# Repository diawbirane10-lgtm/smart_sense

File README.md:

# SmartSense

**Prototype R&D de capteurs industriels — en cours.**

SmartSense est une plateforme de laboratoire pour l'acquisition et le diagnostic de signaux **infrarouges modulés** et **ultrasonores (40 kHz)**. Elle utilise un **STM32G431**, une chaîne analogique dédiée et un **PCB 4 couches** conçu avec KiCad.

## État du projet

| Réalisé | À faire |
|---|---|
| Schémas et PCB KiCad V1 (ERC/DRC : 0 violation signalée) | Fabrication et assemblage de la carte |
| Noyau C : 22 tests réussis sur PC, compilation ARM vérifiée | Intégration firmware et essais sur STM32 |
| Modèles et simulations MATLAB/Simulink | Mesures et validation sur banc |

**Important :** aucun essai physique n'a encore été réalisé. Le prototype n'est pas qualifié pour une application ferroviaire ou de sécurité.

## Fichiers principaux

- [Conception KiCad V1](hardware/V1/SmartSense_V1.kicad_pro) — ouvrir avec **KiCad 10**.
- [Études MATLAB/Simulink](etudes/README.md)
- [Firmware C](firmware/README.md) et [programmation STM32](PROGRAMMATION.md)
- [Prototype et prochaines étapes](ingenierie/PROTOTYPE.md)
- [Revue R&D et limites](ingenierie/revue_RD_20261106/DECISION_ET_REVUE.md)

[Portfolio](https://b-diaw.com)

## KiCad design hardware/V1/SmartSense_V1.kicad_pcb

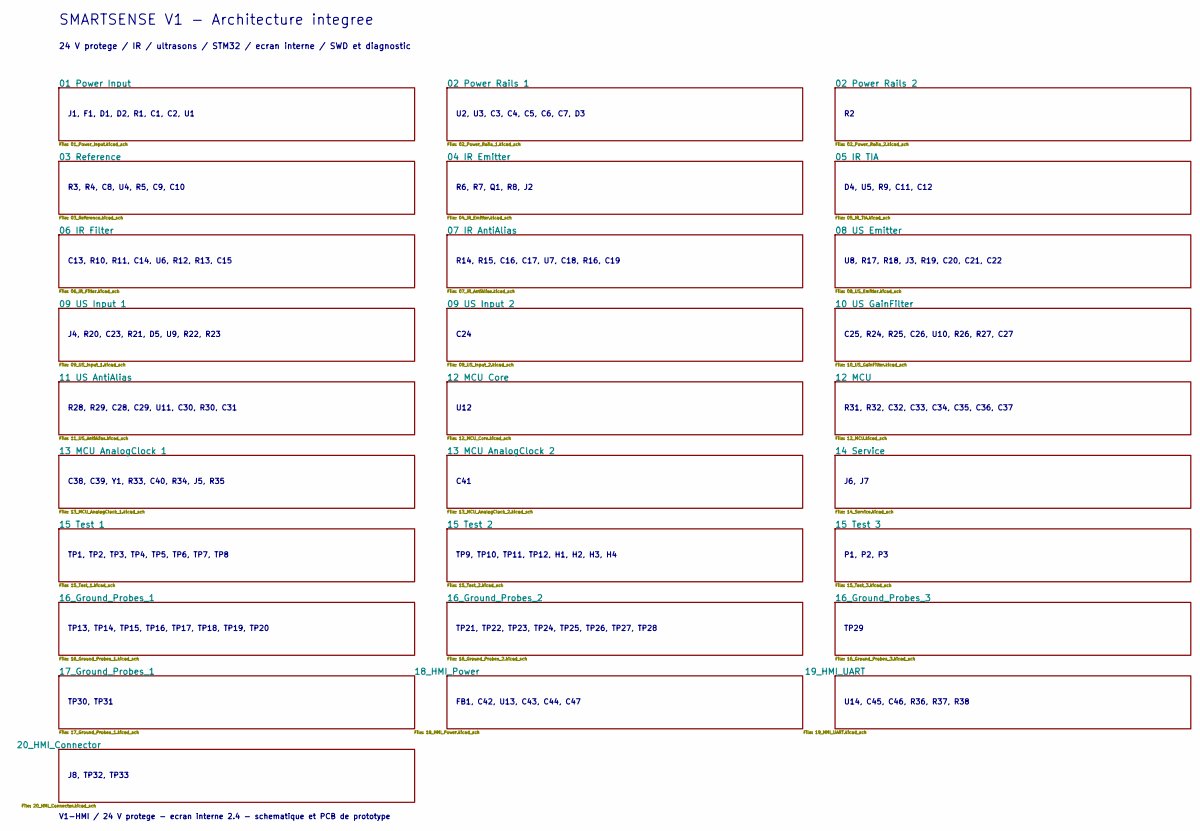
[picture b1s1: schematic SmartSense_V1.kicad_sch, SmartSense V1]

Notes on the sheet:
SMARTSENSE V1 - Architecture integree
24 V protege / IR / ultrasons / STM32 / ecran interne / SWD et diagnostic
V1-HMI / 24 V protege - ecran interne 2.4 - schematique et PCB de prototype
J1, F1, D1, D2, R1, C1, C2, U1
U2, U3, C3, C4, C5, C6, C7, D3
R3, R4, C8, U4, R5, C9, C10
R6, R7, Q1, R8, J2
D4, U5, R9, C11, C12
C13, R10, R11, C14, U6, R12, R13, C15
R14, R15, C16, C17, U7, C18, R16, C19
U8, R17, R18, J3, R19, C20, C21, C22
J4, R20, C23, R21, D5, U9, R22, R23
C24
C25, R24, R25, C26, U10, R26, R27, C27
R28, R29, C28, C29, U11, C30, R30, C31
U12
R31, R32, C32, C33, C34, C35, C36, C37
C38, C39, Y1, R33, C40, R34, J5, R35
C41
J6, J7
TP1, TP2, TP3, TP4, TP5, TP6, TP7, TP8
TP9, TP10, TP11, TP12, H1, H2, H3, H4
P1, P2, P3
TP13, TP14, TP15, TP16, TP17, TP18, TP19, TP20
TP21, TP22, TP23, TP24, TP25, TP26, TP27, TP28
TP29
TP30, TP31
FB1, C42, U13, C43, C44, C47
U14, C45, C46, R36, R37, R38
J8, TP32, TP33

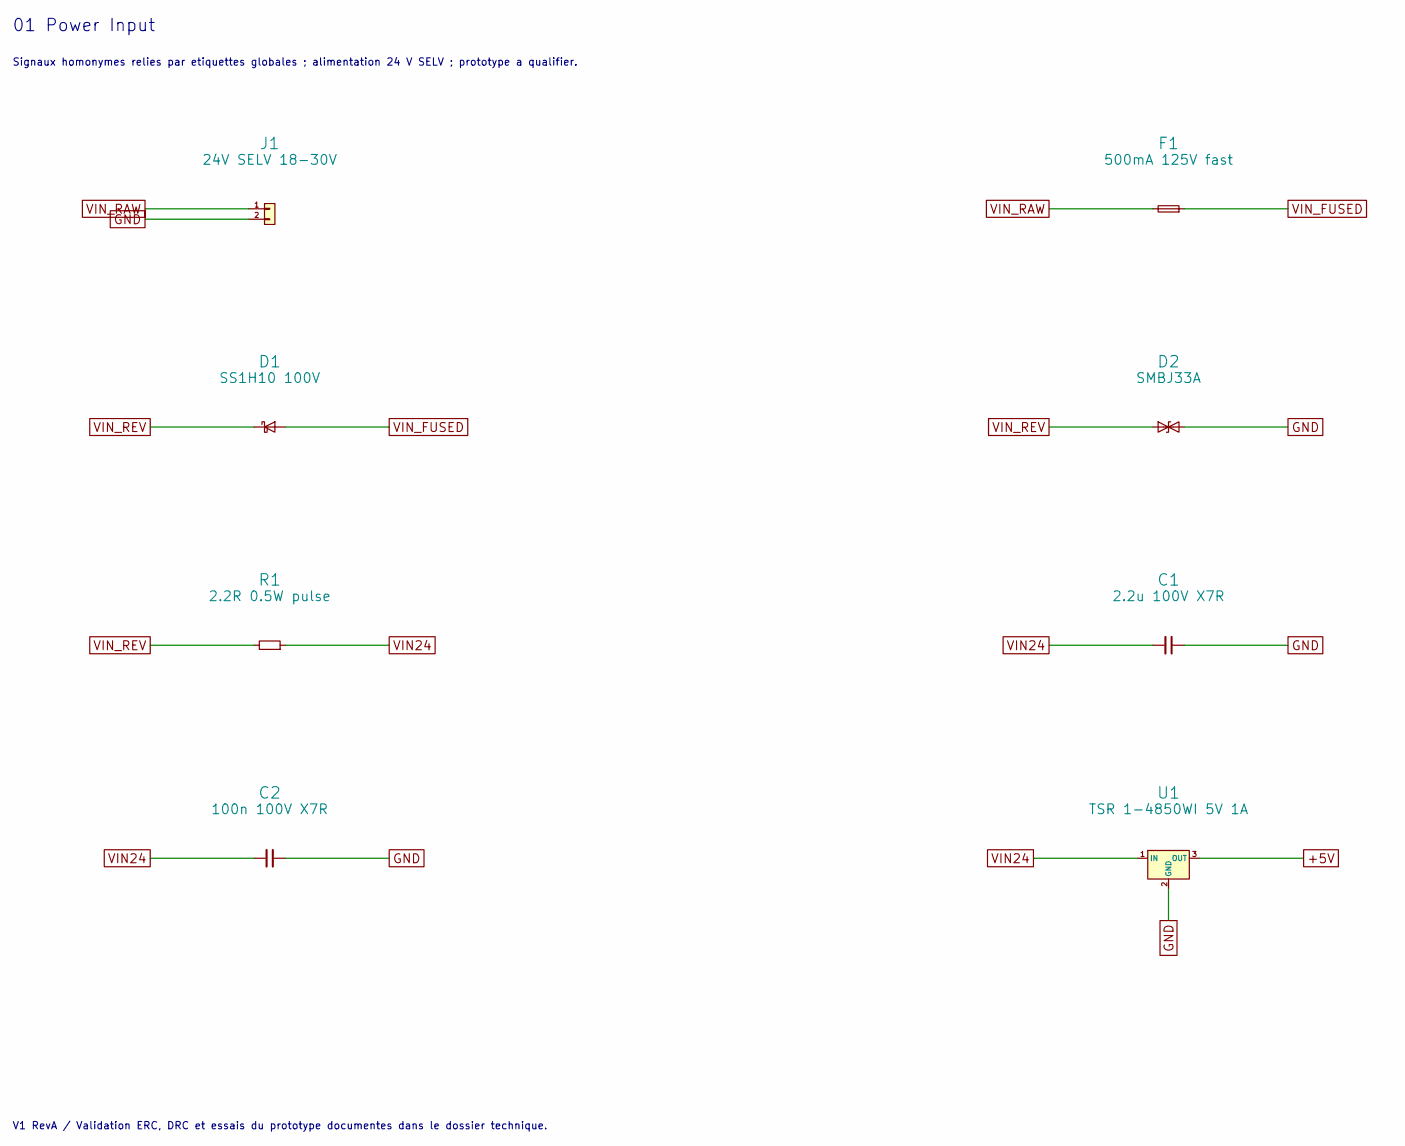
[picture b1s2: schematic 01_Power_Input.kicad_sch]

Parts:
C1: 2.2u 100V X7R; C_1210_3225Metric; MPN C1210C225K1RACTU
C2: 100n 100V X7R; C_0805_2012Metric; MPN C0805C104K1RACTU
D1: SS1H10 100V; D_SMA; MPN SS1H10-E3/61T
D2: SMBJ33A; D_SMB; MPN SMBJ33A-E3/52
F1: 500mA 125V fast; Fuse_Littelfuse-NANO2-451_453; MPN 0451.500MRL
J1: 24V SELV 18-30V; TerminalBlock_Phoenix_MKDS-1,5-2-5.08_1x02_P5.08mm_Horizont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; MPN 1715721
R1: 2.2R 0.5W pulse; R_1210_3225Metric; MPN CRCW12102R20FKEAHP
U1: TSR 1-4850WI 5V 1A; TRACO_TSR1WI_Straight; MPN TSR 1-4850WI

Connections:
+5V: U1.3 (OUT); also elsewhere on the board
GND: C1.2, C2.2, D2.2 (A2), J1.2, U1.2 (GND); also elsewhere on the board
VIN24: C1.1, C2.1, R1.2, U1.1 (IN)
VIN_FUSED: D1.2 (A), F1.2
VIN_RAW: F1.1, J1.1
VIN_REV: D1.1 (K), D2.1 (A1), R1.1

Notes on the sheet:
01 Power Input
Signaux homonymes relies par etiquettes globales ; alimentation 24 V SELV ; prototype a qualifier.
V1 RevA / Validation ERC, DRC et essais du prototype documentes dans le dossier technique.

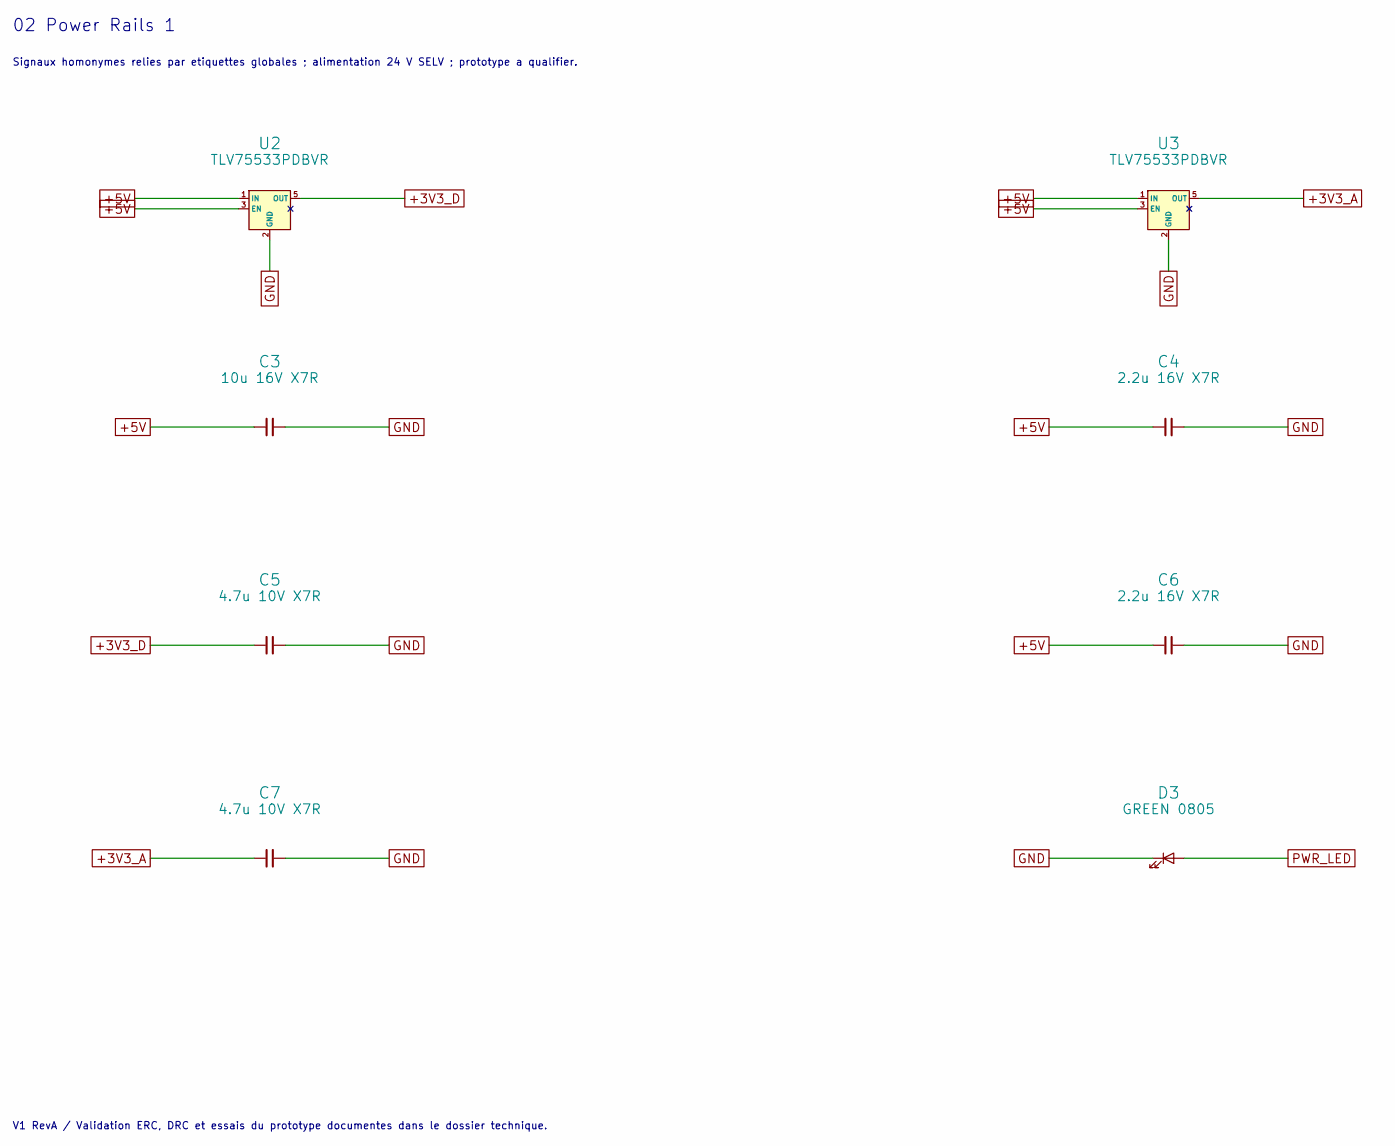
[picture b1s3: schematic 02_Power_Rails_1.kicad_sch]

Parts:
C3: 10u 16V X7R; C_0805_2012Metric; MPN GRM21BR71C106KE51L
C4, C6: 2.2u 16V X7R; C_0805_2012Metric; MPN C0805C225K4RACTU
C5, C7: 4.7u 10V X7R; C_0805_2012Metric; MPN C0805C475K4RACTU
D3: GREEN 0805; LED_0805_2012Metric; MPN APT2012LZGCK
U2, U3: TLV75533PDBVR; SOT-23-5; MPN TLV75533PDBVR

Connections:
+3V3_A: C7.1, U3.5 (OUT); also elsewhere on the board
+3V3_D: C5.1, U2.5 (OUT); also elsewhere on the board
+5V: C3.1, C4.1, C6.1, U2.1 (IN), U2.3 (EN), U3.1 (IN), U3.3 (EN); also elsewhere on the board
GND: C3.2, C4.2, C5.2, C6.2, C7.2, D3.1 (K), U2.2 (GND), U3.2 (GND); also elsewhere on the board
PWR_LED: D3.2 (A); also elsewhere on the board

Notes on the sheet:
02 Power Rails 1
Signaux homonymes relies par etiquettes globales ; alimentation 24 V SELV ; prototype a qualifier.
V1 RevA / Validation ERC, DRC et essais du prototype documentes dans le dossier technique.

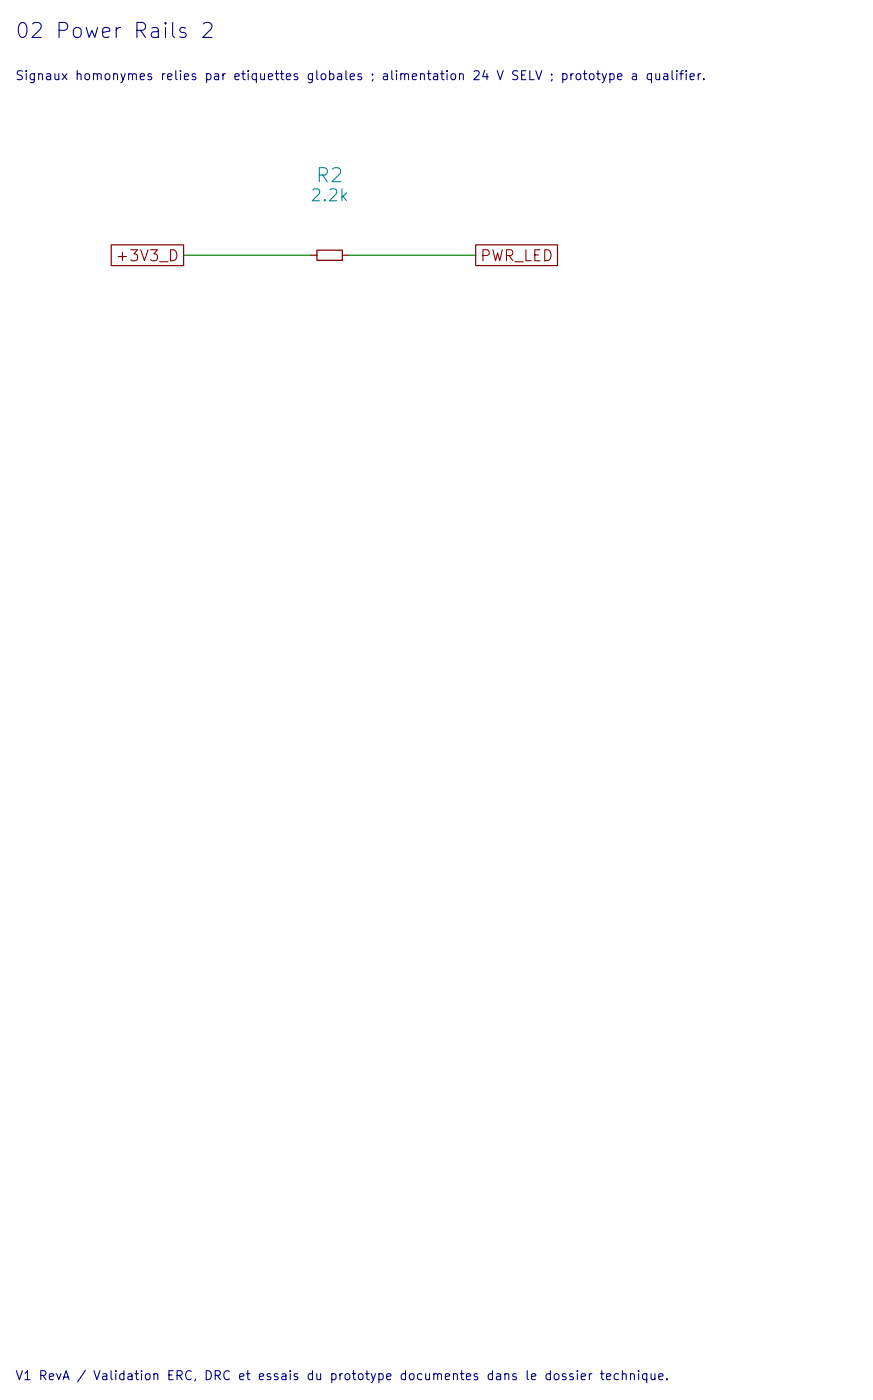
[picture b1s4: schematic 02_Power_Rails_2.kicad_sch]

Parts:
R2: 2.2k; R_0805_2012Metric; MPN RC0805FR-072K2L

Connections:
+3V3_D: R2.1; also elsewhere on the board
PWR_LED: R2.2; also elsewhere on the board

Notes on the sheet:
02 Power Rails 2
Signaux homonymes relies par etiquettes globales ; alimentation 24 V SELV ; prototype a qualifier.
V1 RevA / Validation ERC, DRC et essais du prototype documentes dans le dossier technique.

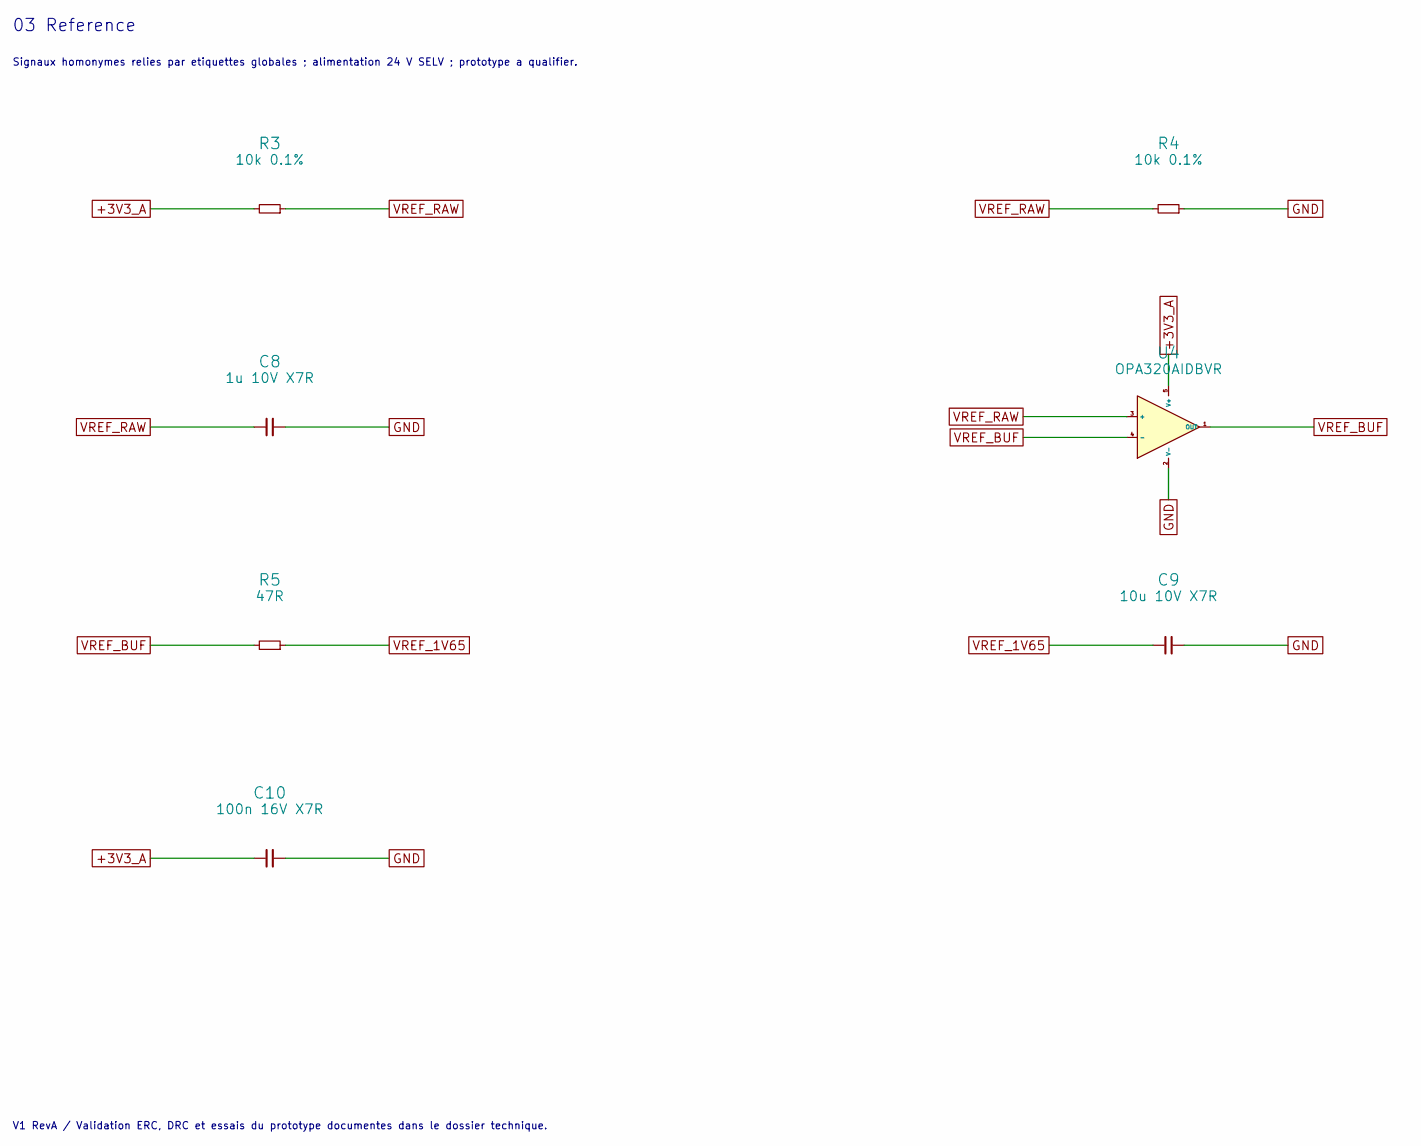
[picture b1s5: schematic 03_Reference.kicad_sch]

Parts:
C8: 1u 10V X7R; C_0805_2012Metric; MPN C0805C105K3RACTU
C9: 10u 10V X7R; C_0805_2012Metric; MPN GRM21BR71C106KE51L
C10: 100n 16V X7R; C_0805_2012Metric; MPN C0805C104K1RACTU
R3, R4: 10k 0.1%; R_0805_2012Metric; MPN RT0805BRD0710KL
R5: 47R; R_0805_2012Metric; MPN RC0805FR-0747RL
U4: OPA320AIDBVR; SOT-23-5; MPN OPA320AIDBVR

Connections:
+3V3_A: C10.1, R3.1, U4.5 (V+); also elsewhere on the board
GND: C8.2, C9.2, C10.2, R4.2, U4.2 (V-); also elsewhere on the board
VREF_1V65: C9.1, R5.2; also elsewhere on the board
VREF_BUF: R5.1, U4.1 (OUT), U4.4 (-)
VREF_RAW: C8.1, R3.2, R4.1, U4.3 (+)

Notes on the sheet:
03 Reference
Signaux homonymes relies par etiquettes globales ; alimentation 24 V SELV ; prototype a qualifier.
V1 RevA / Validation ERC, DRC et essais du prototype documentes dans le dossier technique.

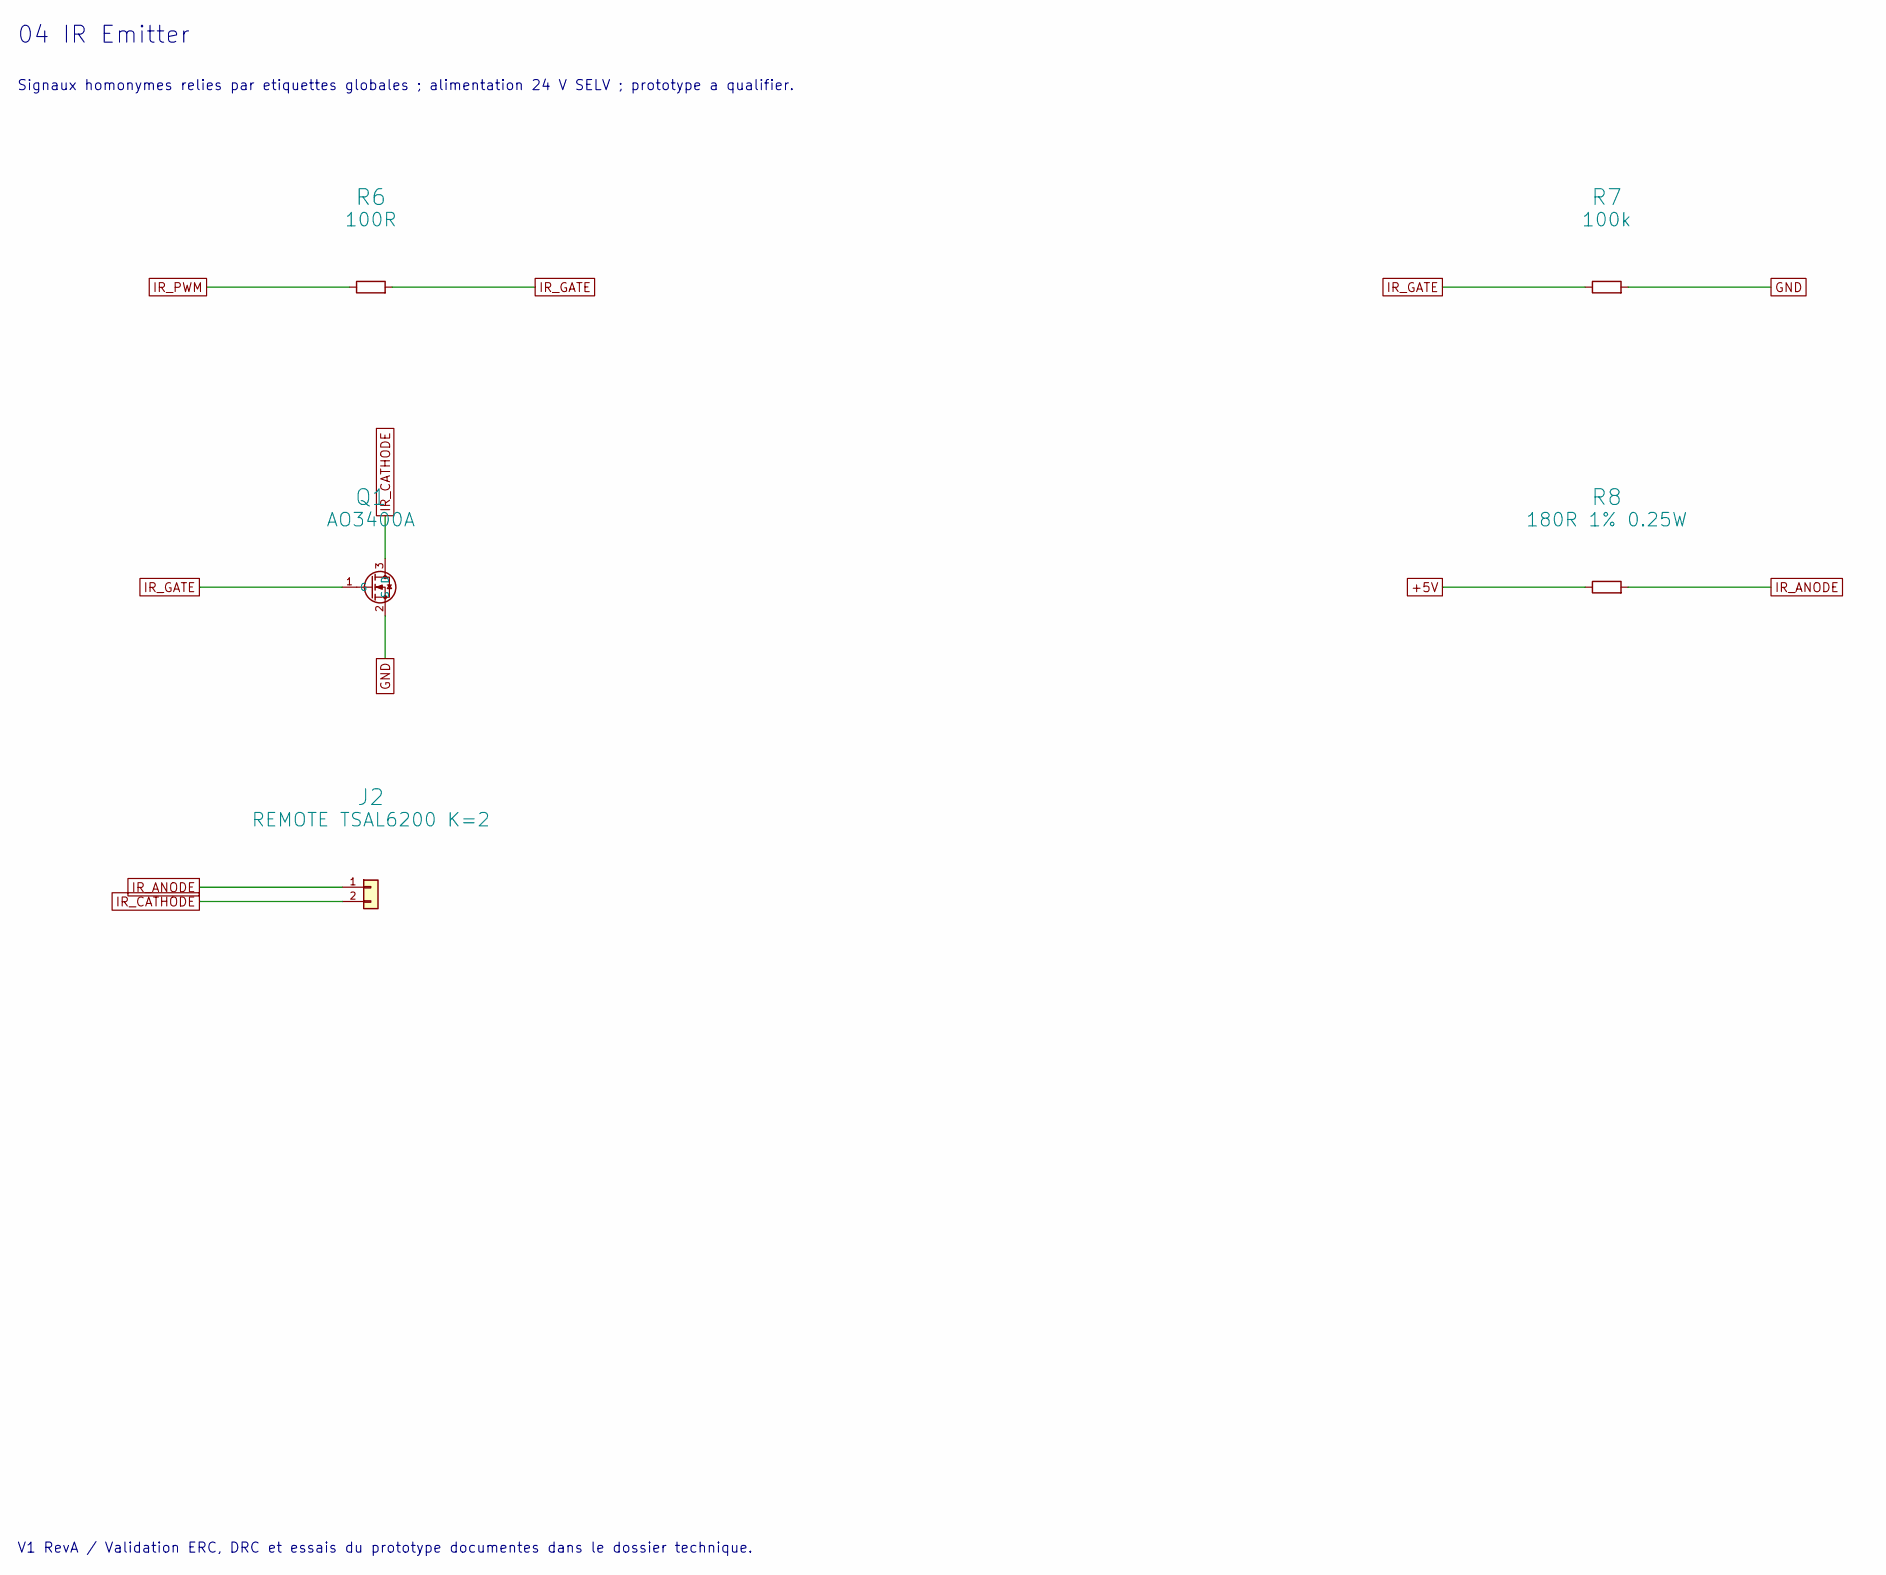
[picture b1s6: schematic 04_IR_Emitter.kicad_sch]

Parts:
J2: REMOTE TSAL6200 K=2; PinHeader_1x02_P2.54mm_Vertical; MPN TSW-102-07-L-S
Q1: AO3400A; SOT-23; MPN AO3400A
R6: 100R; R_0805_2012Metric; MPN RC0805FR-07100RL
R7: 100k; R_0805_2012Metric; MPN RC0805FR-07100KL
R8: 180R 1% 0.25W; R_1206_3216Metric; MPN RC1206FR-07180RL

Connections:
+5V: R8.1; also elsewhere on the board
GND: Q1.2 (S), R7.2; also elsewhere on the board
IR_ANODE: J2.1, R8.2
IR_CATHODE: J2.2, Q1.3 (D)
IR_GATE: Q1.1 (G), R6.2, R7.1
IR_PWM: R6.1; also elsewhere on the board

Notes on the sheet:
04 IR Emitter
Signaux homonymes relies par etiquettes globales ; alimentation 24 V SELV ; prototype a qualifier.
V1 RevA / Validation ERC, DRC et essais du prototype documentes dans le dossier technique.

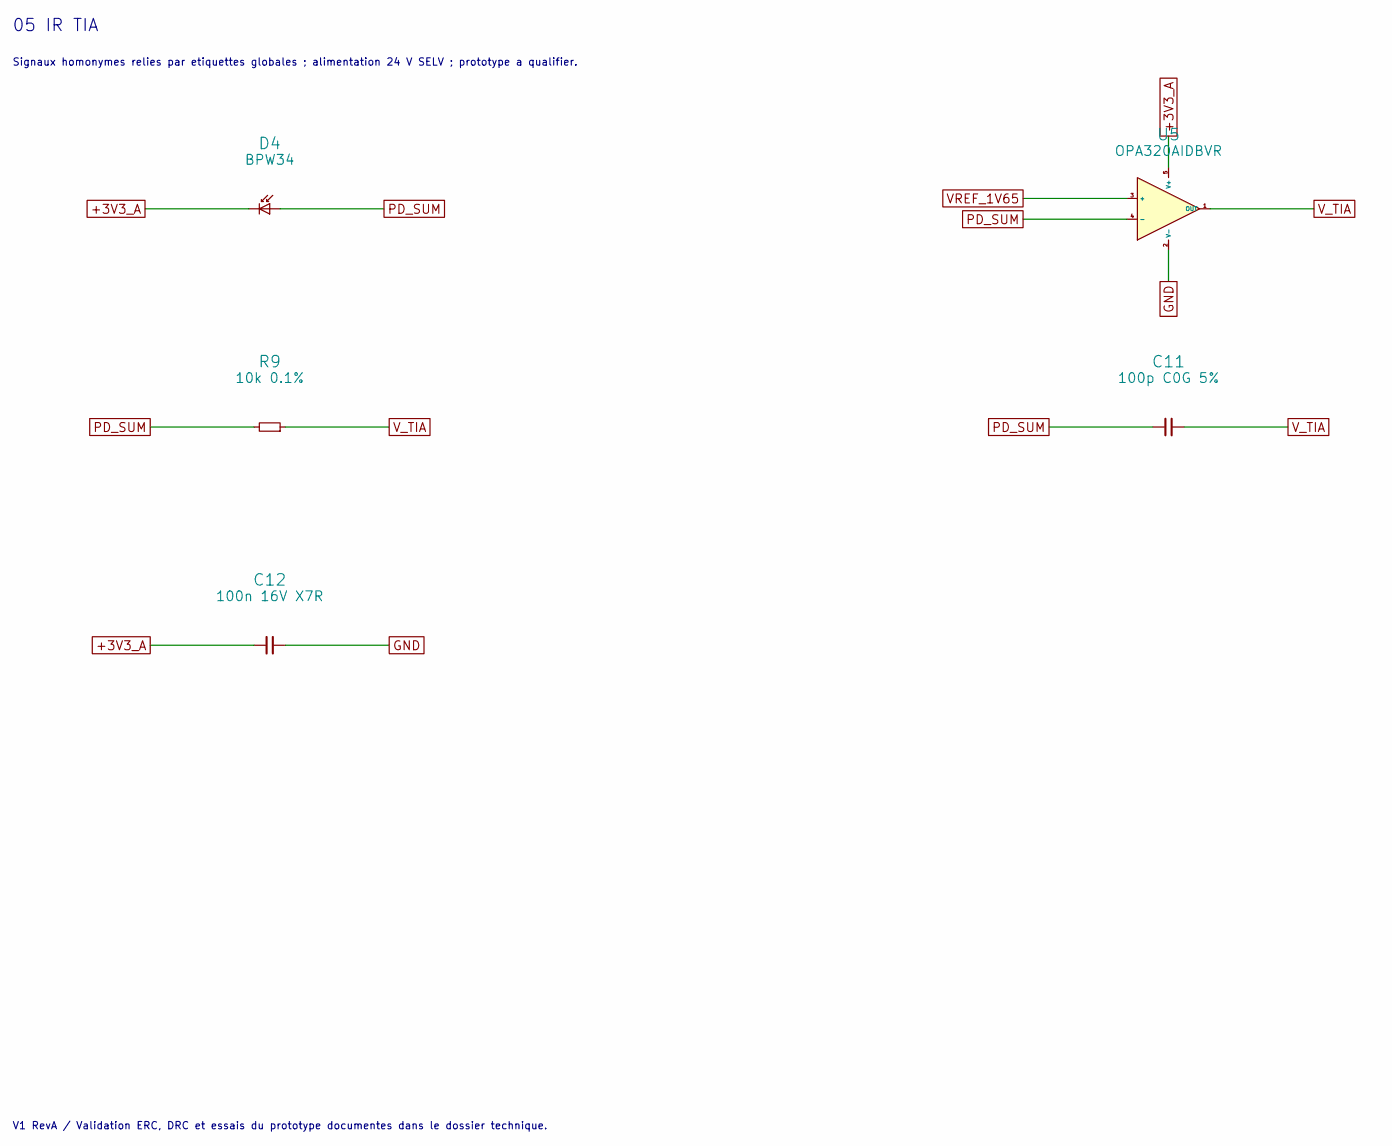
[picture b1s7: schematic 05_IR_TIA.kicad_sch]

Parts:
C11: 100p C0G 5%; C_0805_2012Metric; MPN C0805C101J5GACTU
C12: 100n 16V X7R; C_0805_2012Metric; MPN C0805C104K1RACTU
D4: BPW34; BPW34_THT_P5.08; MPN BPW34
R9: 10k 0.1%; R_0805_2012Metric; MPN RT0805BRD0710KL
U5: OPA320AIDBVR; SOT-23-5; MPN OPA320AIDBVR

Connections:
+3V3_A: C12.1, D4.1 (K), U5.5 (V+); also elsewhere on the board
GND: C12.2, U5.2 (V-); also elsewhere on the board
PD_SUM: C11.1, D4.2 (A), R9.1, U5.4 (-)
VREF_1V65: U5.3 (+); also elsewhere on the board
V_TIA: C11.2, R9.2, U5.1 (OUT); also elsewhere on the board

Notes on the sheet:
05 IR TIA
Signaux homonymes relies par etiquettes globales ; alimentation 24 V SELV ; prototype a qualifier.
V1 RevA / Validation ERC, DRC et essais du prototype documentes dans le dossier technique.

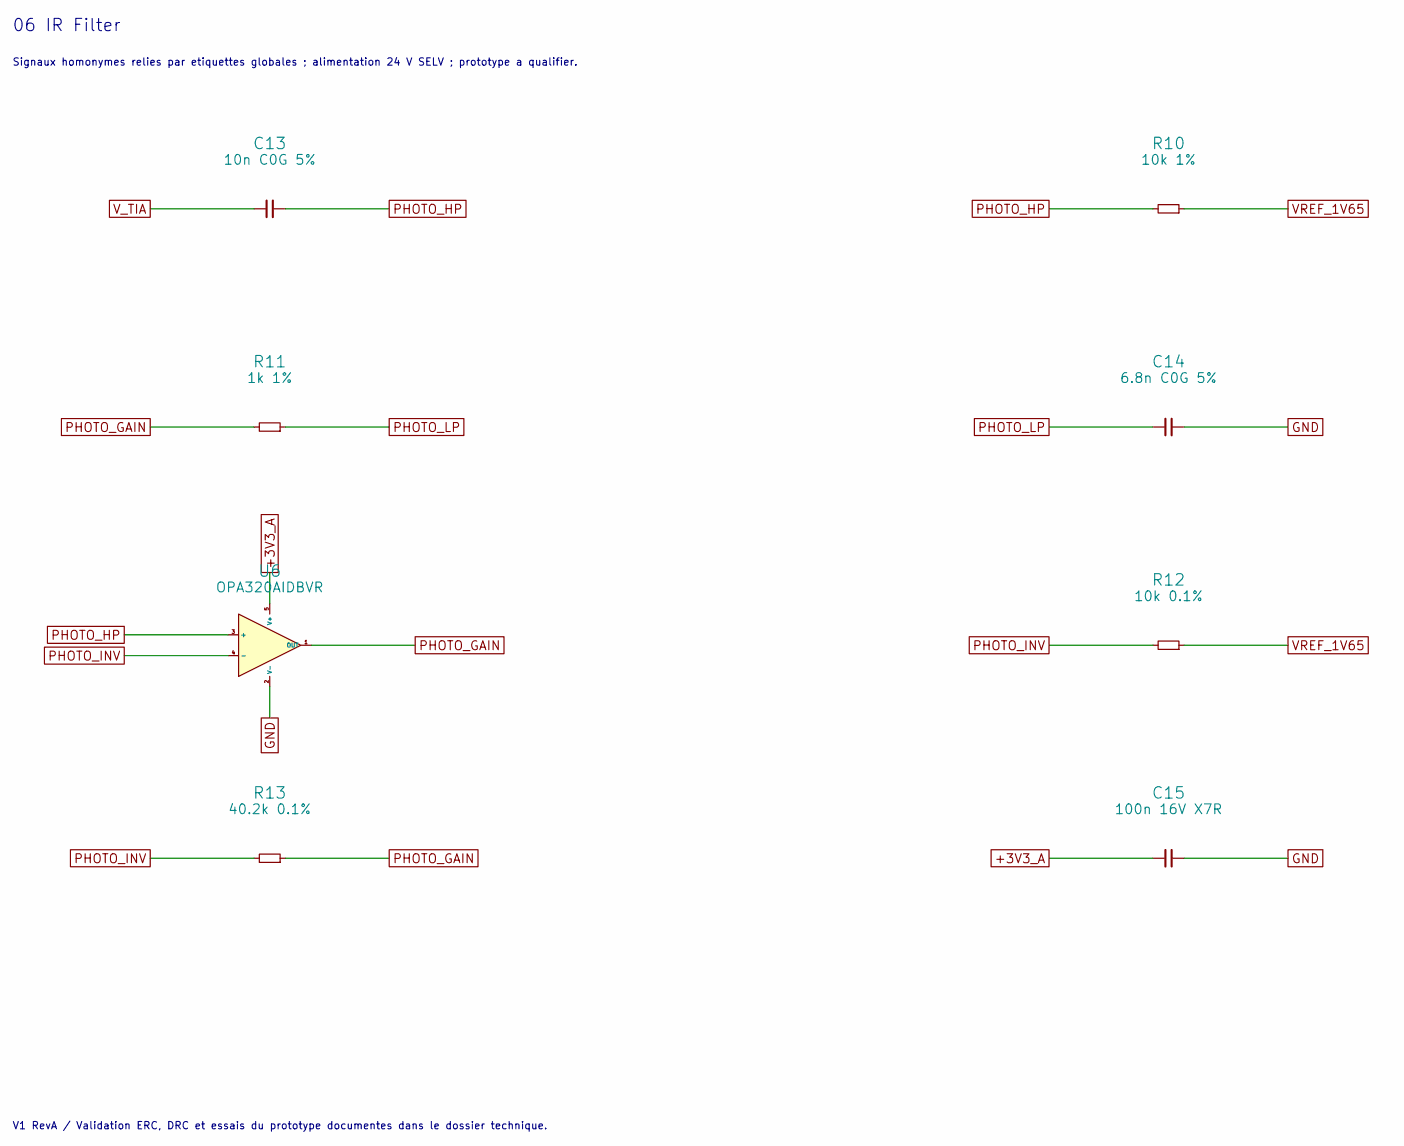
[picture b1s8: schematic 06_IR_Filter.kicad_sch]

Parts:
C13: 10n C0G 5%; C_0805_2012Metric; MPN C0805C103J5GACTU
C14: 6.8n C0G 5%; C_0805_2012Metric; MPN C0805C682J5GACTU
C15: 100n 16V X7R; C_0805_2012Metric; MPN C0805C104K1RACTU
R10: 10k 1%; R_0805_2012Metric; MPN RC0805FR-0710KL
R11: 1k 1%; R_0805_2012Metric; MPN RC0805FR-071KL
R12: 10k 0.1%; R_0805_2012Metric; MPN RT0805BRD0710KL
R13: 40.2k 0.1%; R_0805_2012Metric; MPN RT0805BRD0740K2L
U6: OPA320AIDBVR; SOT-23-5; MPN OPA320AIDBVR

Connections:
+3V3_A: C15.1, U6.5 (V+); also elsewhere on the board
GND: C14.2, C15.2, U6.2 (V-); also elsewhere on the board
PHOTO_GAIN: R11.1, R13.2, U6.1 (OUT)
PHOTO_HP: C13.2, R10.1, U6.3 (+)
PHOTO_INV: R12.1, R13.1, U6.4 (-)
PHOTO_LP: C14.1, R11.2; also elsewhere on the board
VREF_1V65: R10.2, R12.2; also elsewhere on the board
V_TIA: C13.1; also elsewhere on the board

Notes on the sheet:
06 IR Filter
Signaux homonymes relies par etiquettes globales ; alimentation 24 V SELV ; prototype a qualifier.
V1 RevA / Validation ERC, DRC et essais du prototype documentes dans le dossier technique.

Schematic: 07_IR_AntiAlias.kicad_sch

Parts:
C16: 2.2n C0G 2%; C_0805_2012Metric; MPN C0805C222G5GACTU
C17: 1n C0G 2%; C_0805_2012Metric; MPN C0805C102G5GACTU
C18: 100n 16V X7R; C_0805_2012Metric; MPN C0805C104K1RACTU
C19: 1n C0G 5%; C_0805_2012Metric; MPN C0805C102G5GACTU
R14, R15: 5.1k 1%; R_0805_2012Metric; MPN RC0805FR-075K1L
R16: 100R; R_0805_2012Metric; MPN RC0805FR-07100RL
U7: OPA320AIDBVR; SOT-23-5; MPN OPA320AIDBVR

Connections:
+3V3_A: C18.1, U7.5 (V+); also elsewhere on the board
ADC_PHOTO: C19.1, R16.2; also elsewhere on the board
GND: C17.2, C18.2, C19.2, U7.2 (V-); also elsewhere on the board
PHAA_A: C16.1, R14.2, R15.1
PHAA_B: C17.1, R15.2, U7.3 (+)
PHAA_BUF: C16.2, R16.1, U7.1 (OUT), U7.4 (-)
PHOTO_LP: R14.1; also elsewhere on the board

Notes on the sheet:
07 IR AntiAlias
Signaux homonymes relies par etiquettes globales ; alimentation 24 V SELV ; prototype a qualifier.
V1 RevA / Validation ERC, DRC et essais du prototype documentes dans le dossier technique.

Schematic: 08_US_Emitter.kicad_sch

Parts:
C20, C21: 100n 16V X7R; C_0805_2012Metric; MPN C0805C104K1RACTU
C22: 10u 16V X7R; C_0805_2012Metric; MPN GRM21BR71C106KE51L
J3: MA40S4S TX; PinHeader_1x02_P2.54mm_Vertical; MPN TSW-102-07-L-S
R17, R18: 22R 0.25W; R_1206_3216Metric; MPN RC1206FR-0722RL
R19: 100k; R_0805_2012Metric; MPN RC0805FR-07100KL
U8: DRV8837DSGR; Texas_DSG0008A_WSON-8-1EP_2x2mm_P0.5mm_EP0.9x1.6mm; MPN DRV8837DSGR

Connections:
+3V3_D: C21.1, U8.8 (VCC); also elsewhere on the board
+5V: C20.1, C22.1, U8.1 (VM); also elsewhere on the board
GND: C20.2, C21.2, C22.2, R19.2, U8.4 (GND), U8.9 (GND); also elsewhere on the board
US_DRV_A: R17.1, U8.2 (OUT1)
US_DRV_B: R18.1, U8.3 (OUT2)
US_IN1: U8.6 (IN1); also elsewhere on the board
US_IN2: U8.5 (IN2); also elsewhere on the board
US_SLEEP: R19.1, U8.7 (~SLEEP); also elsewhere on the board
US_TX_A: J3.1, R17.2
US_TX_B: J3.2, R18.2

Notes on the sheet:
08 US Emitter
Signaux homonymes relies par etiquettes globales ; alimentation 24 V SELV ; prototype a qualifier.
V1 RevA / Validation ERC, DRC et essais du prototype documentes dans le dossier technique.

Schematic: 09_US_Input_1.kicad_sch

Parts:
C23: 1n C0G 5%; C_0805_2012Metric; MPN C0805C102G5GACTU
D5: PESD5V0S1BA; D_SOD-323; MPN PESD5V0S1BA
J4: MA40S4R RX; PinHeader_1x02_P2.54mm_Vertical; MPN TSW-102-07-L-S
R20: 4.7k; R_0805_2012Metric; MPN RC0805FR-074K7L
R21: 1M 1%; R_0805_2012Metric; MPN RC0805FR-071ML
R22: 10k 0.1%; R_0805_2012Metric; MPN RT0805BRD0710KL
R23: 100k 0.1%; R_0805_2012Metric; MPN RT0805BRD07100KL
U9: OPA320AIDBVR; SOT-23-5; MPN OPA320AIDBVR

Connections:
+3V3_A: U9.5 (V+); also elsewhere on the board
GND: D5.2 (A2), J4.2, U9.2 (V-); also elsewhere on the board
US_AMP1: R23.2, U9.1 (OUT); also elsewhere on the board
US_INV1: R22.1, R23.1, U9.4 (-)
US_RX_BIAS: C23.2, R21.1, U9.3 (+)
US_RX_LIMIT: C23.1, R20.2
US_RX_RAW: D5.1 (A1), J4.1, R20.1
VREF_1V65: R21.2, R22.2; also elsewhere on the board

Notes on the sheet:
09 US Input 1
Signaux homonymes relies par etiquettes globales ; alimentation 24 V SELV ; prototype a qualifier.
V1 RevA / Validation ERC, DRC et essais du prototype documentes dans le dossier technique.

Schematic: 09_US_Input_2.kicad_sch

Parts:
C24: 100n 16V X7R; C_0805_2012Metric; MPN C0805C104K1RACTU

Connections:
+3V3_A: C24.1; also elsewhere on the board
GND: C24.2; also elsewhere on the board

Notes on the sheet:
09 US Input 2
Signaux homonymes relies par etiquettes globales ; alimentation 24 V SELV ; prototype a qualifier.
V1 RevA / Validation ERC, DRC et essais du prototype documentes dans le dossier technique.

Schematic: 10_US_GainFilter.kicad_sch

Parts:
C25, C26: 1n C0G 5%; C_0805_2012Metric; MPN C0805C102G5GACTU
C27: 100n 16V X7R; C_0805_2012Metric; MPN C0805C104K1RACTU
R24: 6.8k 1%; R_0805_2012Metric; MPN RC0805FR-076K8L
R25: 2.2k 1%; R_0805_2012Metric; MPN RC0805FR-072K2L
R26: 10k 0.1%; R_0805_2012Metric; MPN RT0805BRD0710KL
R27: 33k 0.1%; R_0805_2012Metric; MPN RT0805BRD0733KL
U10: OPA320AIDBVR; SOT-23-5; MPN OPA320AIDBVR

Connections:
+3V3_A: C27.1, U10.5 (V+); also elsewhere on the board
GND: C26.2, C27.2, U10.2 (V-); also elsewhere on the board
US_AMP1: C25.1; also elsewhere on the board
US_GAIN2: R27.2, U10.1 (OUT); also elsewhere on the board
US_HP: C25.2, R24.1, R25.1
US_INV2: R26.1, R27.1, U10.4 (-)
US_LP: C26.1, R25.2, U10.3 (+)
VREF_1V65: R24.2, R26.2; also elsewhere on the board

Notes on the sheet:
10 US GainFilter
Signaux homonymes relies par etiquettes globales ; alimentation 24 V SELV ; prototype a qualifier.
V1 RevA / Validation ERC, DRC et essais du prototype documentes dans le dossier technique.

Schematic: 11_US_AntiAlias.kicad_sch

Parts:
C28: 2.2n C0G 2%; C_0805_2012Metric; MPN C0805C222G5GACTU
C29: 1n C0G 2%; C_0805_2012Metric; MPN C0805C102G5GACTU
C30: 100n 16V X7R; C_0805_2012Metric; MPN C0805C104K1RACTU
C31: 22n C0G 5%; C_0805_2012Metric; MPN C0805C223J5GACTU
R28, R29: 2.49k 1%; R_0805_2012Metric; MPN RC0805FR-072K49L
R30: 100R; R_0805_2012Metric; MPN RC0805FR-07100RL
U11: OPA320AIDBVR; SOT-23-5; MPN OPA320AIDBVR

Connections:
+3V3_A: C30.1, U11.5 (V+); also elsewhere on the board
ADC_US: C31.1, R30.2; also elsewhere on the board
GND: C29.2, C30.2, C31.2, U11.2 (V-); also elsewhere on the board
USAA_A: C28.1, R28.2, R29.1
USAA_B: C29.1, R29.2, U11.3 (+)
USAA_BUF: C28.2, R30.1, U11.1 (OUT), U11.4 (-)
US_GAIN2: R28.1; also elsewhere on the board

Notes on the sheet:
11 US AntiAlias
Signaux homonymes relies par etiquettes globales ; alimentation 24 V SELV ; prototype a qualifier.
V1 RevA / Validation ERC, DRC et essais du prototype documentes dans le dossier technique.

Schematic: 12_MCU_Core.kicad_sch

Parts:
U12: STM32G431CBT6; LQFP-48_7x7mm_P0.5mm; MPN STM32G431CBT6

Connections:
+3V3_A: U12.20 (VREF+), U12.21 (VDDA); also elsewhere on the board
+3V3_D: U12.1 (VBAT), U12.24 (VDD), U12.36 (VDD), U12.48 (VDD); also elsewhere on the board
ADC_PHOTO: U12.8 (PA0); also elsewhere on the board
ADC_TEMP: U12.16 (PB0); also elsewhere on the board
ADC_US: U12.9 (PA1); also elsewhere on the board
BOOT0: U12.45 (PB8); also elsewhere on the board
GND: U12.19 (VSSA), U12.23 (VSS), U12.35 (VSS), U12.47 (VSS); also elsewhere on the board
HMI_ENABLE: U12.44 (PB7); also elsewhere on the board
HMI_UART_RX: U12.32 (PA10); also elsewhere on the board
HMI_UART_TX: U12.31 (PA9); also elsewhere on the board
HSE_IN: U12.5 (PF0); also elsewhere on the board
IR_PWM: U12.43 (PB6); also elsewhere on the board
NRST: U12.7 (PG10); also elsewhere on the board
SWCLK: U12.38 (PA14); also elsewhere on the board
SWDIO: U12.37 (PA13); also elsewhere on the board
UART_RX: U12.11 (PA3); also elsewhere on the board
UART_TX: U12.10 (PA2); also elsewhere on the board
US_IN1: U12.30 (PA8); also elsewhere on the board
US_IN2: U12.15 (PA7); also elsewhere on the board
US_SLEEP: U12.42 (PB5); also elsewhere on the board

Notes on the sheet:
12 MCU Core
Signaux homonymes relies par etiquettes globales ; alimentation 24 V SELV ; prototype a qualifier.
V1 RevA / Validation ERC, DRC et essais du prototype documentes dans le dossier technique.

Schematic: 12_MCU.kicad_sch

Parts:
C32, C33, C34, C35, C36: 100n 16V X7R; C_0805_2012Metric; MPN C0805C104K1RACTU
C37: 4.7u 10V X7R; C_0805_2012Metric; MPN C0805C475K4RACTU
R31, R32: 10k; R_0805_2012Metric; MPN RC0805FR-0710KL

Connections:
+3V3_D: C33.1, C34.1, C35.1, C36.1, C37.1, R32.1; also elsewhere on the board
BOOT0: R31.1; also elsewhere on the board
GND: C32.2, C33.2, C34.2, C35.2, C36.2, C37.2, R31.2; also elsewhere on the board
NRST: C32.1, R32.2; also elsewhere on the board

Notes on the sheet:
12 MCU
Signaux homonymes relies par etiquettes globales ; alimentation 24 V SELV ; prototype a qualifier.
V1 RevA / Validation ERC, DRC et essais du prototype documentes dans le dossier technique.

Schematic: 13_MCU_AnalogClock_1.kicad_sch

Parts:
C38, C40: 100n 16V X7R; C_0805_2012Metric; MPN C0805C104K1RACTU
C39: 1u 10V X7R; C_0805_2012Metric; MPN C0805C105K3RACTU
J5: 103AT-2 10k B3435 1%; PinHeader_1x02_P2.54mm_Vertical; MPN TSW-102-07-L-S
R33: 33R; R_0805_2012Metric; MPN RC0805FR-0733RL
R34: 10k 0.1%; R_0805_2012Metric; MPN RT0805BRD0710KL
R35: 1k; R_0805_2012Metric; MPN RC0805FR-071KL
Y1: ASV-8.000MHZ-EJ-T; Oscillator_SMD_Abracon_ASV-4Pin_7.0x5.1mm; MPN ASV-8.000MHZ-EJ-T

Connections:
+3V3_A: C38.1, C39.1, R34.1; also elsewhere on the board
+3V3_D: C40.1, Y1.1 (EN), Y1.4 (Vdd); also elsewhere on the board
ADC_TEMP: R35.2; also elsewhere on the board
GND: C38.2, C39.2, C40.2, J5.2, Y1.2 (GND); also elsewhere on the board
HSE_IN: R33.2; also elsewhere on the board
HSE_OSC: R33.1, Y1.3 (OUT)
NTC_RAW: J5.1, R34.2, R35.1

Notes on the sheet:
13 MCU AnalogClock 1
Signaux homonymes relies par etiquettes globales ; alimentation 24 V SELV ; prototype a qualifier.
V1 RevA / Validation ERC, DRC et essais du prototype documentes dans le dossier technique.

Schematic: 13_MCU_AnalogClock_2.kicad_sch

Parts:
C41: 100n 16V X7R; C_0805_2012Metric; MPN C0805C104K1RACTU

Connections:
ADC_TEMP: C41.1; also elsewhere on the board
GND: C41.2; also elsewhere on the board

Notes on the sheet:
13 MCU AnalogClock 2
Signaux homonymes relies par etiquettes globales ; alimentation 24 V SELV ; prototype a qualifier.
V1 RevA / Validation ERC, DRC et essais du prototype documentes dans le dossier technique.

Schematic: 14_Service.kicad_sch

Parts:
J6: Cortex SWD 1.27mm; SWD_M50_3500542; MPN M50-3500542
J7: UART 3V3 SERVICE; PinHeader_1x04_P2.54mm_Vertical; MPN TSW-104-07-L-S

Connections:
+3V3_D: J6.1; also elsewhere on the board
GND: J6.3, J6.5, J6.9, J7.1, J7.4; also elsewhere on the board
NRST: J6.10; also elsewhere on the board
SWCLK: J6.4; also elsewhere on the board
SWDIO: J6.2; also elsewhere on the board
UART_RX: J7.3; also elsewhere on the board
UART_TX: J7.2; also elsewhere on the board

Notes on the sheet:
14 Service
Signaux homonymes relies par etiquettes globales ; alimentation 24 V SELV ; prototype a qualifier.
V1 RevA / Validation ERC, DRC et essais du prototype documentes dans le dossier technique.

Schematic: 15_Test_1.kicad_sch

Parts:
TP1, TP2, TP3, TP4, TP5: GND; TestPoint_THTPad_D1.0mm_Drill0.5mm; MPN GND
TP6: +5V; TestPoint_Pad_D1.0mm; MPN +5V
TP7: +3V3_A; TestPoint_Pad_D1.0mm; MPN +3V3_A
TP8: +3V3_D; TestPoint_Pad_D1.0mm; MPN +3V3_D

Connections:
+3V3_A: TP7.1; also elsewhere on the board
+3V3_D: TP8.1; also elsewhere on the board
+5V: TP6.1; also elsewhere on the board
GND: TP1.1, TP2.1, TP3.1, TP4.1, TP5.1; also elsewhere on the board

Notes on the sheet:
15 Test 1
Signaux homonymes relies par etiquettes globales ; alimentation 24 V SELV ; prototype a qualifier.
V1 RevA / Validation ERC, DRC et essais du prototype documentes dans le dossier technique.

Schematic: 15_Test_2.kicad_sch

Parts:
H1, H2, H3, H4: M3 NPTH; MountingHole_3.2mm_M3; MPN M3 NPTH
TP9: VREF_1V65; TestPoint_Pad_D1.0mm; MPN VREF_1V65
TP10: V_TIA; TestPoint_Pad_D1.0mm; MPN V_TIA
TP11: ADC_PHOTO; TestPoint_Pad_D1.0mm; MPN ADC_PHOTO
TP12: ADC_US; TestPoint_Pad_D1.0mm; MPN ADC_US

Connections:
ADC_PHOTO: TP11.1; also elsewhere on the board
ADC_US: TP12.1; also elsewhere on the board
VREF_1V65: TP9.1; also elsewhere on the board
V_TIA: TP10.1; also elsewhere on the board

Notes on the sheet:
15 Test 2
Signaux homonymes relies par etiquettes globales ; alimentation 24 V SELV ; prototype a qualifier.
V1 RevA / Validation ERC, DRC et essais du prototype documentes dans le dossier technique.
